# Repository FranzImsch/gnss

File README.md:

# [GNSS Rev. B](https://github.com/FranzImsch/gnss)

# Overview

[ZED-F9P](https://www.u-blox.com/sites/default/files/ZED-F9P-04B_DataSheet_UBX-21044850.pdf)\-based GNSS dev board with [ISM330DHCX](https://www.st.com/resource/en/datasheet/ism330dhcx.pdf) 6-DoF IMU, [BMM150](https://www.bosch-sensortec.com/media/boschsensortec/downloads/datasheets/bst-bmm150-ds001.pdf) Magnetometer and [DPS310](https://www.infineon.com/dgdl/Infineon-DPS310-DS-v01_00-EN.pdf?fileId=5546d462576f34750157750826c42242) pressure sensor.

As a basic UI, the OLED (1.5") can be used along with a navigation switch, more advanced usage requires a web interface. The device features a microSD card reader for data logging.

The ESP32 is used as the microcontroller because of its WiFi and Bluetooth capability that enables data to be streamed onto a device (phone, tablet, …) wirelessly.

The component selection is partly influenced by the semiconductor shortage. The software is yet to be worked on and also the documentation should receive some attention.

# Hardware

The device consists of a stackup of three PCBs. A detailed view is provided by the [3D-model](https://a360.co/38VXSXv). The third PCB is not relevant for the function, as it only serves as a mounting piece for the battery.

 The uppermost PCB of the stackup is where the OLED is mounted along with the navigation switch and some status LEDs. The photo shows the backside of this PCB with the IO ports and their isolation. Also found here is the barometric pressure sensor (top), a port expander and the 12V step-up converter for the OLED. One may ignore the little bodge at the top. :)

 The picture shows the main PCB where the ZED module is located (right-hand side). On the left the ESP32 module can be found along with the FTDI chips for both the ESP and the UART1 port of the ZED-F9P. The bottom left is where the USB hub chip is placed. On the bottom-right there is the power section, consisting of a step-down converter, a power path manager, a fuel gauge for the battery and some super low-noise LDOs for the ZED-F9P.

## Battery

The function of the battery circuitry was tested extensively and no issues were found. The device correctly stops power when the cutoff voltage is reaced (3.2 V, depends on the voltage supervisor). During charging, the unit does not exceed ca. 60°C at the hottest point (which is the power path IC).

## Documentation and Resources

[Schematic](https://franz.science/gnss/Schematic.pdf)  
[iBom PCB #1](https://franz.science/gnss/PCB-1/bom/index.html)  
[iBom PCB #2](https://franz.science/gnss/PCB-2/bom/index.html)

[3D model](https://a360.co/38VXSXv)

## Changelog (Rev A to B)

* Added LiPo battery to enable standalone operation
* Replaced BNO055 with ISM330DHCX and BMM150 due to their superior performance
* Removed SHT40 as the first revision revealed that the board heats up too much for temperature or humidity measurement (Can be added via exposed i2c connector)
* Added USB hub to board
* Protected ZED a bit more against electrical damage (isolating and filtering IO, LDO as power supply)
* many minor improvements

# GNSS in General

Useful literature:

* https://doi.org/10.1007/978-3-211-73017-1
* https://content.u-blox.com/sites/default/files/products/documents/GPS-Compendium_Book\_(GPS-X-02007).pdf?hash=undefined

---

# Licence

Copyright Franz Imschweiler 2022.

This source describes Open Hardware and is licensed under the CERN-OHL-S v2 or any later version. You may redistribute and modify this source and make products using it under the terms of the CERN-OHL-S v2 or any later version (https://ohwr.org/cern_ohl_s_v2.txt).

This source is distributed WITHOUT ANY EXPRESS OR IMPLIED WARRANTY, INCLUDING OF MERCHANTABILITY, SATISFACTORY QUALITY AND FITNESS FOR A PARTICULAR PURPOSE. Please see the CERN-OHL-S v2 for applicable conditions.

Source location: https://github.com/FranzImsch/gnss

As per CERN-OHL-S v2 section 4, should You produce hardware based on this source, You must where practicable maintain the Source Location visible on the external case of the GNSS Receiver or other products you make using this source.

---

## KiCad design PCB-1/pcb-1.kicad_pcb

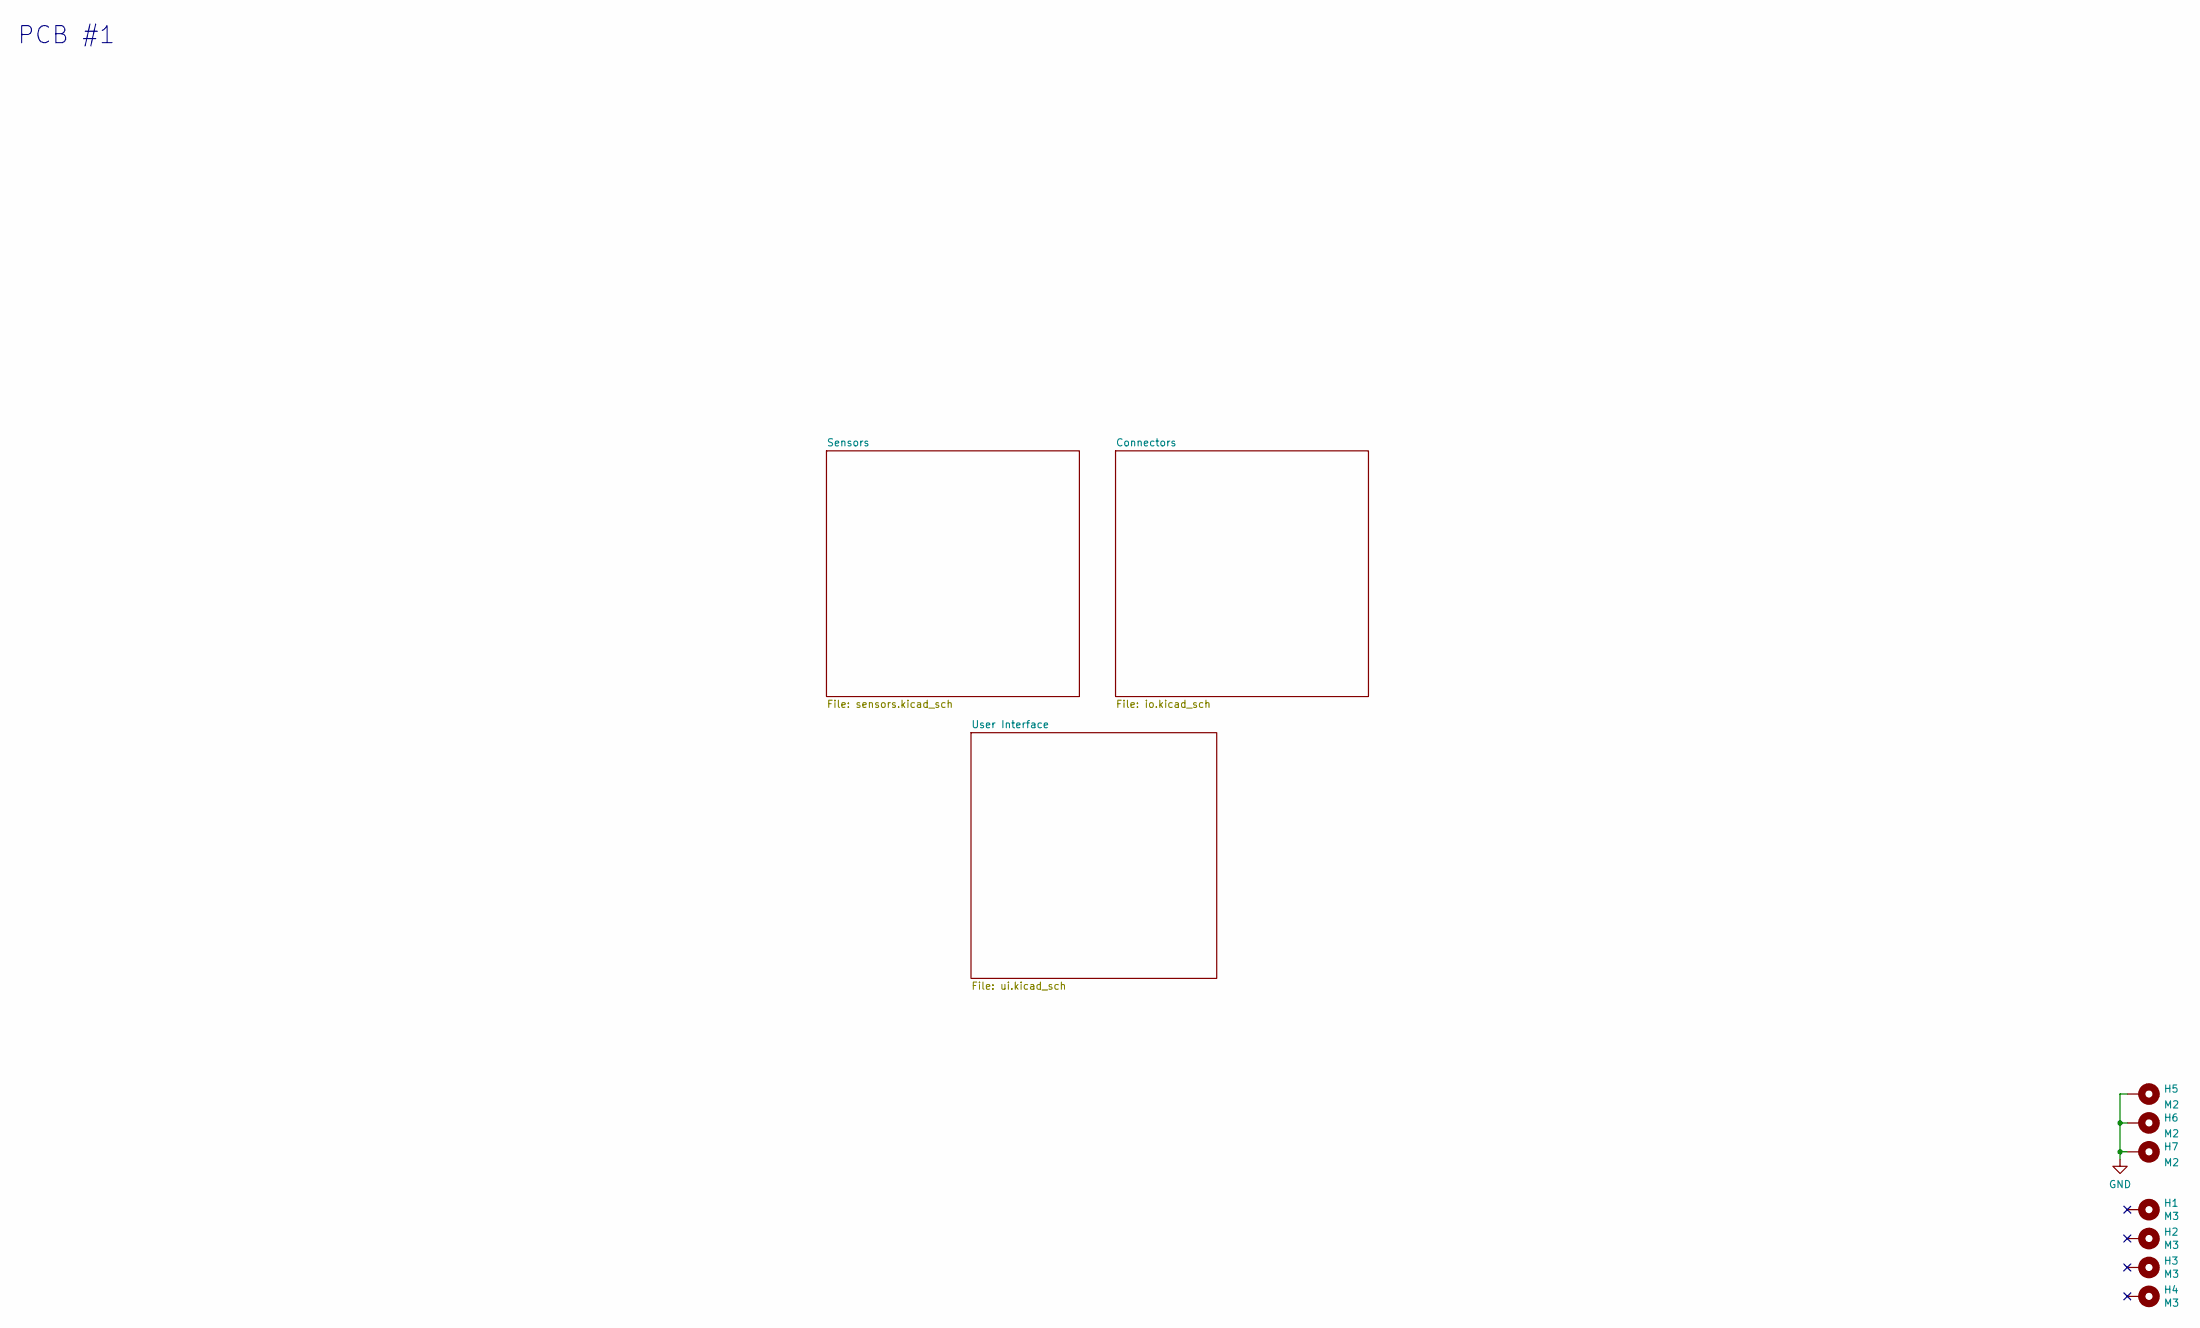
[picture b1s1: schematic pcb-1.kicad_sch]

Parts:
H1, H2, H3, H4: M3; MountingHole_3.2mm_M3_Pad_Via_NoSilk
H5, H6, H7: M2; MountingHole_2.2mm_M2_Pad_Via_NoSilk

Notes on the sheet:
PCB #1

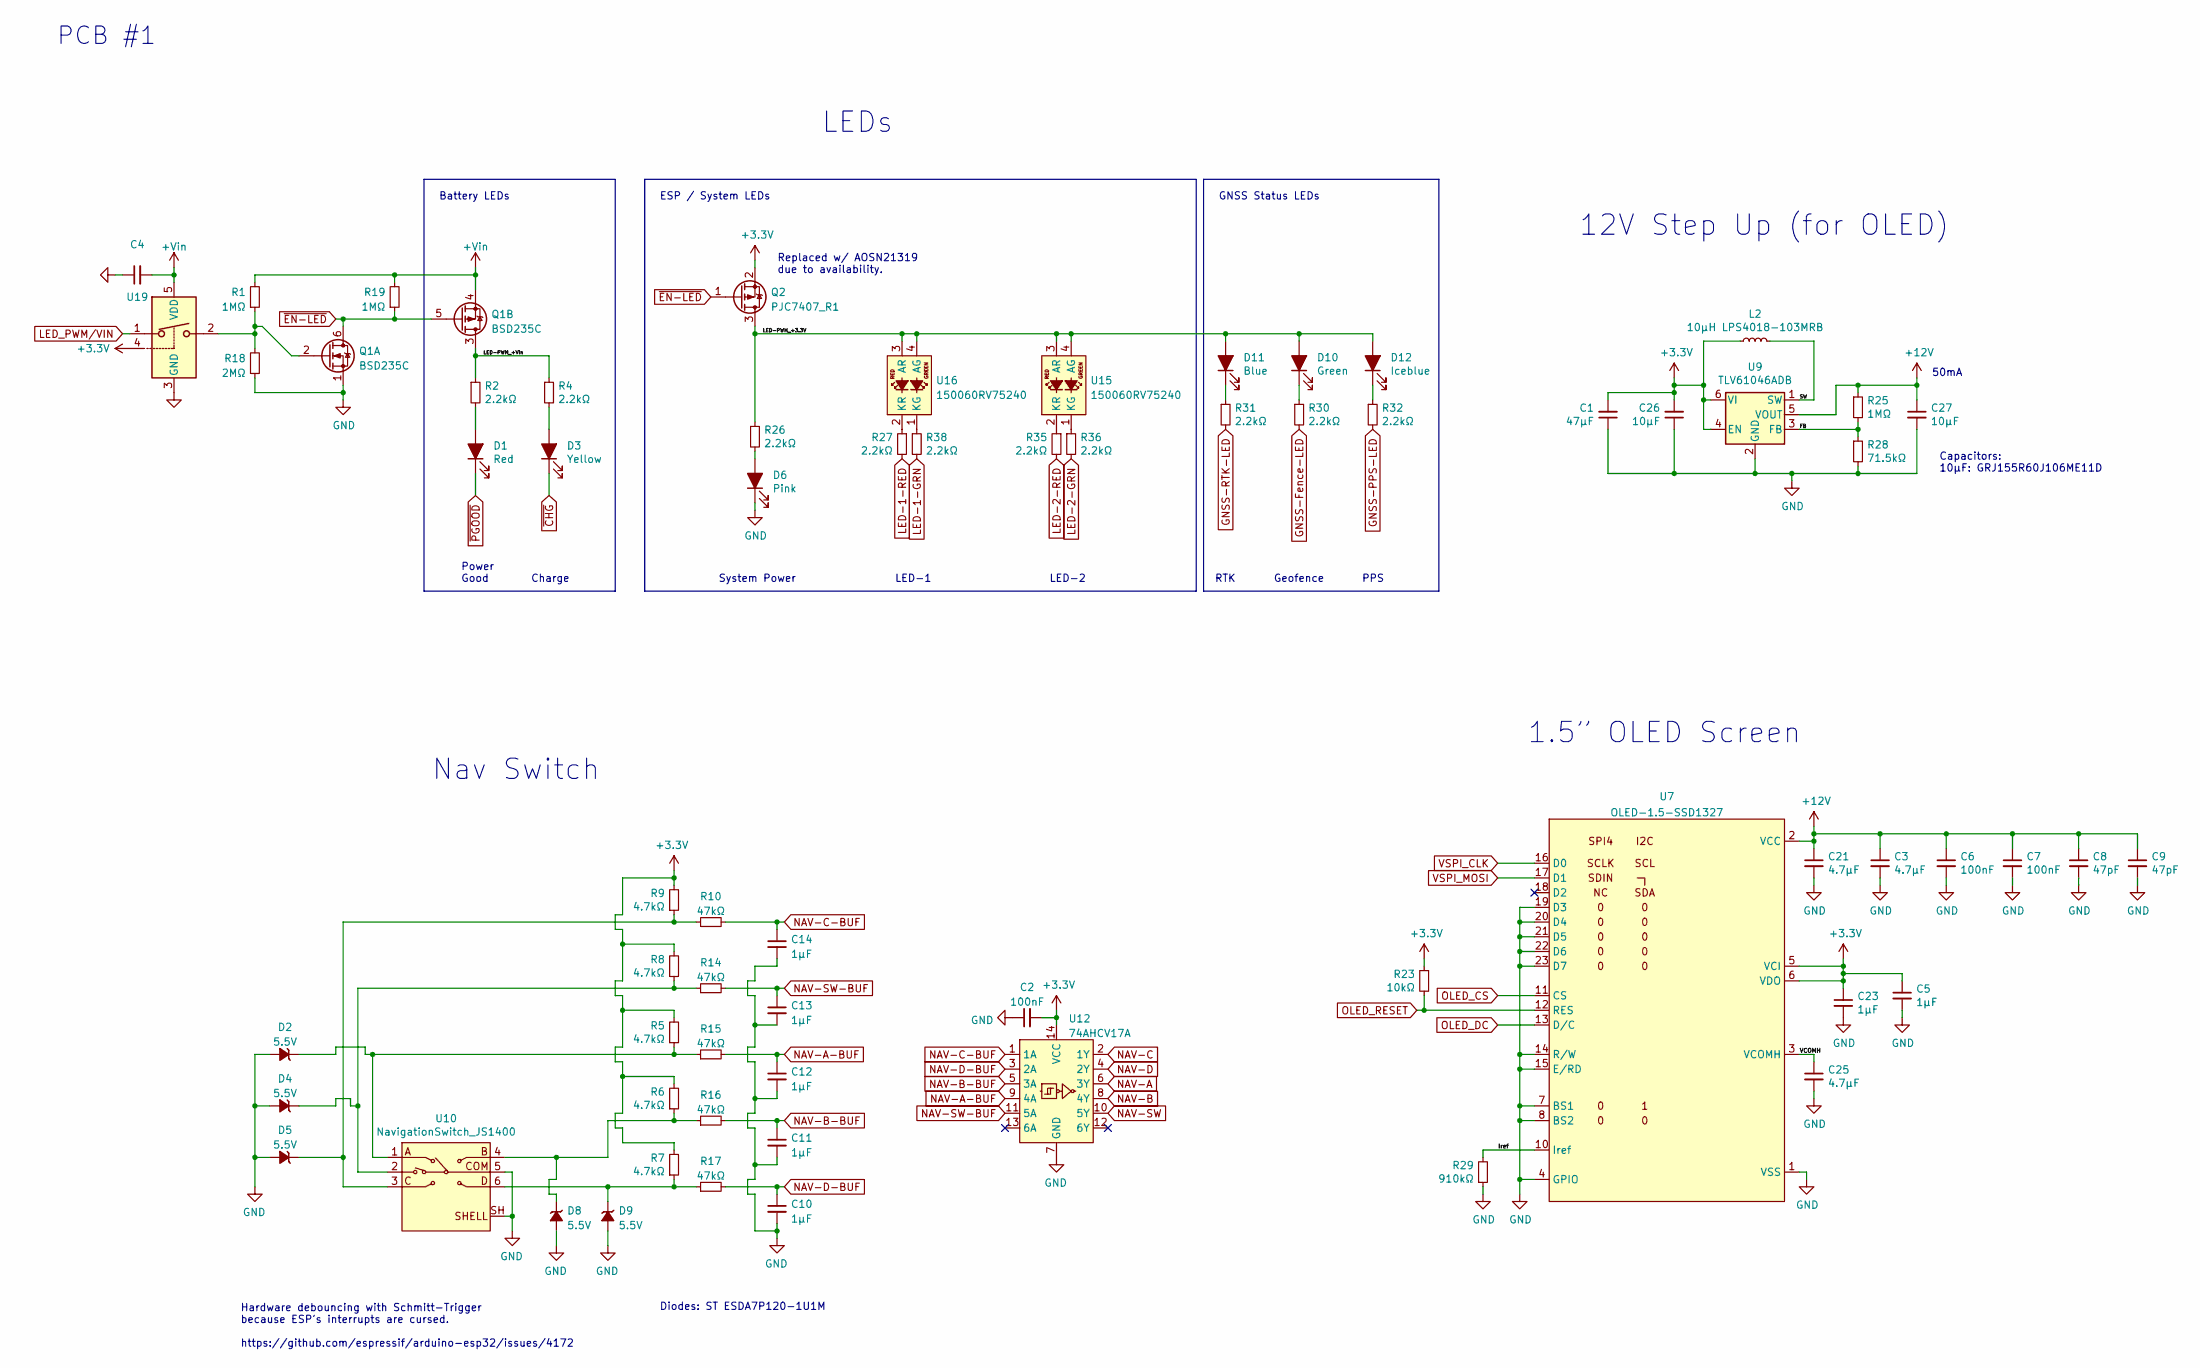
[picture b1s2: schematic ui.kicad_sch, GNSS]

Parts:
C1: 47µF; C_1206_3216Metric_NoSilk
C2: 100nF; C_0402_1005Metric_NoSilk
C3, C21: 4.7µF; C_1206_3216Metric_NoSilk
C4: (no value)
C5, C23: 1µF; C_0603_1608Metric_NoSilk
C6, C7: 100nF; C_0603_1608Metric_NoSilk
C8, C9: 47pF; C_0402_1005Metric_NoSilk
C10, C11, C12, C13, C14: 1µF; C_0402_1005Metric_NoSilk
C25: 4.7µF; C_0603_1608Metric_NoSilk
C26: 10µF; C_0402_1005Metric_NoSilk
C27: 10µF; C_1206_3216Metric_NoSilk
D1: Red; LED_0603_1608Metric_SmallSilk
D2, D4, D5, D8, D9: 5.5V; ST_QFN1610_1_NoSilk
D3: Yellow; LED_0603_1608Metric_SmallSilk
D6: Pink; LED_0603_1608Metric_SmallSilk
D10: Green; LED_0603_1608Metric_SmallSilk
D11: Blue; LED_0603_1608Metric_SmallSilk
D12: Iceblue; LED_0603_1608Metric_SmallSilk
L2: 10µH LPS4018-103MRB; L_Coilcraft_LPS4018_NoSilk
Q1: BSD235C; SOT-363_SC-70-6
Q2: PJC7407_R1; SOT-323_SC-70_NoSilk
R1, R19, R25: 1MΩ; R_0402_1005Metric_NoSilk
R2, R4, R26, R27, R30, R31, R32, R35, R36, R38: 2.2kΩ; R_0402_1005Metric_NoSilk
R5, R6, R7, R8, R9: 4.7kΩ; R_0402_1005Metric_NoSilk
R10, R14, R15, R16, R17: 47kΩ; R_0402_1005Metric_NoSilk
R18: 2MΩ; R_0402_1005Metric_NoSilk
R23: 10kΩ; R_0402_1005Metric_NoSilk
R28: 71.5kΩ; R_0402_1005Metric_NoSilk
R29: 910kΩ; R_0402_1005Metric_NoSilk
U7: OLED-1.5-SSD1327; OLED_SSD1327_1.5
U9: TLV61046ADB; SOT-23-6_NoSilk
U10: NavigationSwitch_JS1400; NavigationStick_ESwitch-JS1400AFQ
U12: 74AHCV17A; TSSOP-14_4.4x5mm_P0.65mm_NoSilk
U15, U16: 150060RV75240; 150060RV75240_Smaller
U19: (no value)

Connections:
+3V3: C1.2, C2.2, C5.1, C23.1, C26.2, L2.1, Q2.2 (S), R5.2, R6.2, R7.2, R8.2, R9.2, R23.1, U7.5 (VCI), U7.6 (VDO), U9.4 (EN), U9.6 (VI), U12.14 (VCC), U19.4; also elsewhere on the board
+12V: C3.1, C6.1, C7.1, C8.1, C9.1, C21.1, C27.1, R25.1, U7.2 (VCC), U7.24 (VCC), U9.5 (VOUT)
+Vin: C4.2, Q1.4 (SP), R1.2, R19.2, U19.5 (VDD); also elsewhere on the board
/User Interface/FB: R25.2, R28.1, U9.3 (FB)
/User Interface/Iref: R29.2, U7.10 (Iref)
/User Interface/LED-PWM_+3.3V: D10.2 (A), D11.2 (A), D12.2 (A), Q2.3 (D), R26.1, U15.3 (AR), U15.4 (AG), U16.3 (AR), U16.4 (AG)
/User Interface/LED-PWM_+Vin: Q1.3 (DP), R2.1, R4.1
/User Interface/SW: L2.2, U9.1 (SW)
/User Interface/VCOMH: C25.1, U7.3 (VCOMH)
GNSS-Fence-LED: R30.2; also elsewhere on the board
GNSS-PPS-LED: R32.2; also elsewhere on the board
GNSS-RTK-LED: R31.2; also elsewhere on the board
LED-1-GRN: R38.2; also elsewhere on the board
LED-1-RED: R27.2; also elsewhere on the board
LED-2-GRN: R36.2; also elsewhere on the board
LED-2-RED: R35.2; also elsewhere on the board
LED_PWM/VIN: U19.1; also elsewhere on the board
NAV-A: U12.6 (3Y); also elsewhere on the board
NAV-A-BUF: C12.1, R15.2, U12.9 (4A)
NAV-B: U12.8 (4Y); also elsewhere on the board
NAV-B-BUF: C11.1, R16.2, U12.5 (3A)
NAV-C: U12.2 (1Y); also elsewhere on the board
NAV-C-BUF: C14.1, R10.2, U12.1 (1A)
NAV-D: U12.4 (2Y); also elsewhere on the board
NAV-D-BUF: C10.1, R17.2, U12.3 (2A)
NAV-SW: U12.10 (5Y); also elsewhere on the board
NAV-SW-BUF: C13.1, R14.2, U12.11 (5A)
unnamed: D1.2 (A), R2.2
unnamed: D2.1 (K), R5.1, R15.1, U10.1 (A)
unnamed: D3.2 (A), R4.2
unnamed: D4.1 (K), R8.1, R14.1, U10.2 (BTN)
unnamed: D5.1 (K), R9.1, R10.1, U10.3 (C)
unnamed: D6.2 (A), R26.2
unnamed: D8.1 (K), R6.1, R16.1, U10.4 (B)
unnamed: D9.1 (K), R7.1, R17.1, U10.6 (D)
unnamed: D10.1 (K), R30.1
unnamed: D11.1 (K), R31.1
unnamed: D12.1 (K), R32.1
unnamed: Q1.2 (GN), R1.1, R18.2, U19.2
unnamed: R27.1, U16.2 (KR)
unnamed: R35.1, U15.2 (KR)
unnamed: R36.1, U15.1 (KG)
unnamed: R38.1, U16.1 (KG)
OLED_CS: U7.11 (CS); also elsewhere on the board
OLED_DC: U7.13 (D/C); also elsewhere on the board
OLED_RESET: R23.2, U7.12 (RES); also elsewhere on the board
VSPI_CLK: U7.16 (D0); also elsewhere on the board
VSPI_MOSI: U7.17 (D1); also elsewhere on the board
~CHG: D3.1 (K); also elsewhere on the board
~EN-LED: Q1.5 (GP), Q1.6 (DN), Q2.1 (G), R19.1
~PGOOD: D1.1 (K); also elsewhere on the board

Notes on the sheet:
Hardware debouncing with Schmitt-Trigger because ESP's interrupts are cursed. https://github.com/espressif/arduino-esp32/issues/4172
Nav Switch
PCB #1
ESP / System LEDs
PPS
1.5” OLED Screen
RTK
System Power
Diodes: ST ESDA7P120-1U1M
50mA
Replaced w/ AOSN21319 due to availability.
12V Step Up (for OLED)
Battery LEDs
Power Good
Charge
GNSS Status LEDs
Capacitors: 10µF: GRJ155R60J106ME11D
LEDs
Geofence
LED-1
LED-2

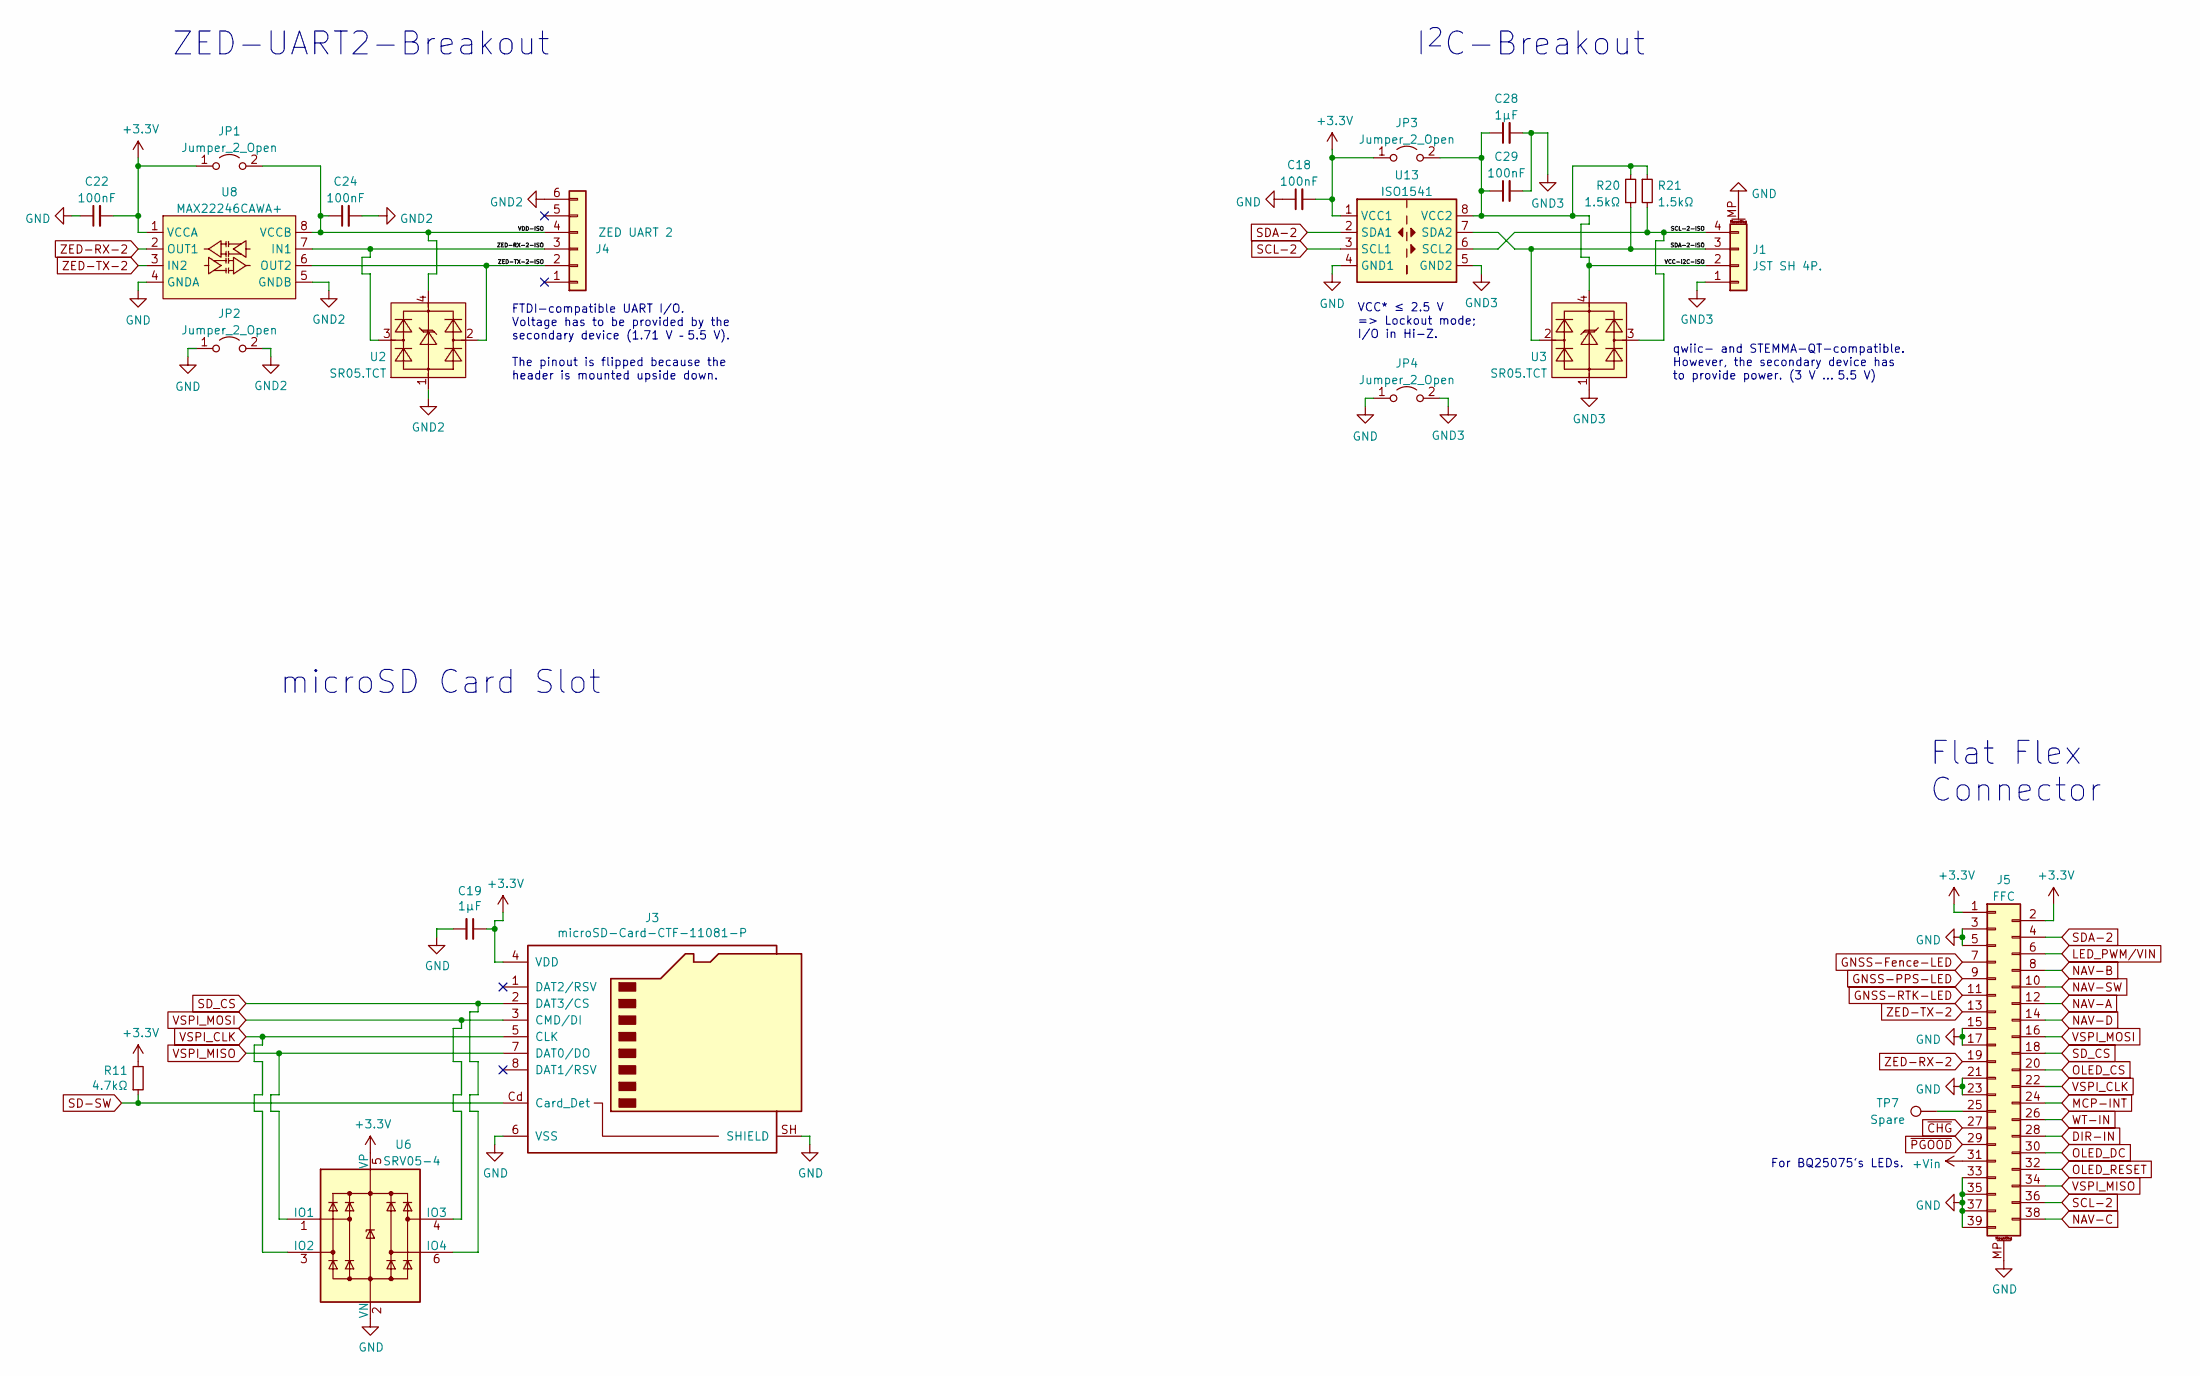
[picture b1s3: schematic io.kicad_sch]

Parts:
C18, C22, C24, C29: 100nF; C_0402_1005Metric_NoSilk
C19, C28: 1µF; C_0402_1005Metric_NoSilk
J1: JST SH 4P.; JST_SH_SM04B-SRSS-TB_1x04-1MP_P1.00mm_Horizontal
J3: microSD-Card-CTF-11081-P
J4: ZED UART 2; PinSocket_2.54mm_01x06_Horizontal_SMD
J5: FFC; 5025983993
JP1, JP2, JP3, JP4: Jumper_2_Open; R_0805_2012Metric_NoSilk_DNP
R11: 4.7kΩ; R_0402_1005Metric_NoSilk
R20, R21: 1.5kΩ; R_0402_1005Metric_NoSilk
TP7: Spare; TestPoint_Pad_D1.0mm_NoSIlk
U2, U3: SR05.TCT; SOT143-4L-slim
U6: SRV05-4; SOT-23-6_NoSilk
U8: MAX22246CAWA+; SOIC-8W_3.9x_P1.27mm_NoSilk
U13: ISO1541; SOIC-8_3.9x4.9mm_P1.27mm_NoSilk

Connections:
+3V3: C18.2, C19.1, C22.2, J3.4 (VDD), J5.1, J5.2, JP1.1 (A), JP3.1 (A), R11.2, U6.5 (VP), U8.1 (VCCA), U13.1 (VCC1); also elsewhere on the board
+Vin: J5.31; also elsewhere on the board
/Connectors/SCL-2-ISO: J1.4, R21.2, U3.3 (CH2), U13.6 (SCL2)
/Connectors/SDA-2-ISO: J1.3, R20.1, U3.2 (CH1), U13.7 (SDA2)
/Connectors/VCC-I2C-ISO: C28.1, C29.1, J1.2, JP3.2 (B), R20.2, R21.1, U3.4 (VBUS), U13.8 (VCC2)
/Connectors/VDD-ISO: C24.1, J4.4, JP1.2 (B), U2.4 (VBUS), U8.8 (VCCB)
/Connectors/ZED-RX-2-ISO: J4.3, U2.3 (CH2), U8.7 (IN1)
/Connectors/ZED-TX-2-ISO: J4.2, U2.2 (CH1), U8.6 (OUT2)
DIR-IN: J5.28; also elsewhere on the board
GND2: C24.2, J4.6, JP2.2 (B), U2.1 (GND), U8.5 (GNDB)
GND3: C28.2, C29.2, J1.1, JP4.2 (B), U3.1 (GND), U13.5 (GND2)
GNSS-Fence-LED: J5.7; also elsewhere on the board
GNSS-PPS-LED: J5.9; also elsewhere on the board
GNSS-RTK-LED: J5.11; also elsewhere on the board
LED_PWM/VIN: J5.6; also elsewhere on the board
MCP-INT: J5.24; also elsewhere on the board
NAV-A: J5.12; also elsewhere on the board
NAV-B: J5.8; also elsewhere on the board
NAV-C: J5.38; also elsewhere on the board
NAV-D: J5.14; also elsewhere on the board
NAV-SW: J5.10; also elsewhere on the board
unnamed: J5.25, TP7.1
OLED_CS: J5.20; also elsewhere on the board
OLED_DC: J5.30; also elsewhere on the board
OLED_RESET: J5.32; also elsewhere on the board
SCL-2: J5.36, U13.3 (SCL1); also elsewhere on the board
SD-SW: J3.Cd (Card_Det), R11.1; also elsewhere on the board
SDA-2: J5.4, U13.2 (SDA1); also elsewhere on the board
SD_CS: J3.2 (DAT3/CS), J5.18, U6.6 (IO4)
VSPI_CLK: J3.5 (CLK), J5.22, U6.3 (IO2); also elsewhere on the board
VSPI_MISO: J3.7 (DAT0/DO), J5.34, U6.1 (IO1)
VSPI_MOSI: J3.3 (CMD/DI), J5.16, U6.4 (IO3); also elsewhere on the board
WT-IN: J5.26; also elsewhere on the board
ZED-RX-2: J5.19, U8.2 (OUT1)
ZED-TX-2: J5.13, U8.3 (IN2)
~CHG: J5.27; also elsewhere on the board
~PGOOD: J5.29; also elsewhere on the board

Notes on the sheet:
I^{2}C-Breakout
VCC* ≤ 2.5 V => Lockout mode; I/O in Hi-Z.
qwiic- and STEMMA-QT-compatible. However, the secondary device has to provide power. (3 V … 5.5 V)
Flat Flex Connector
For BQ25075's LEDs.
microSD Card Slot
FTDI-compatible UART I/O. Voltage has to be provided by the secondary device (1.71 V – 5.5 V). The pinout is flipped because the header is mounted upside down.
ZED-UART2-Breakout

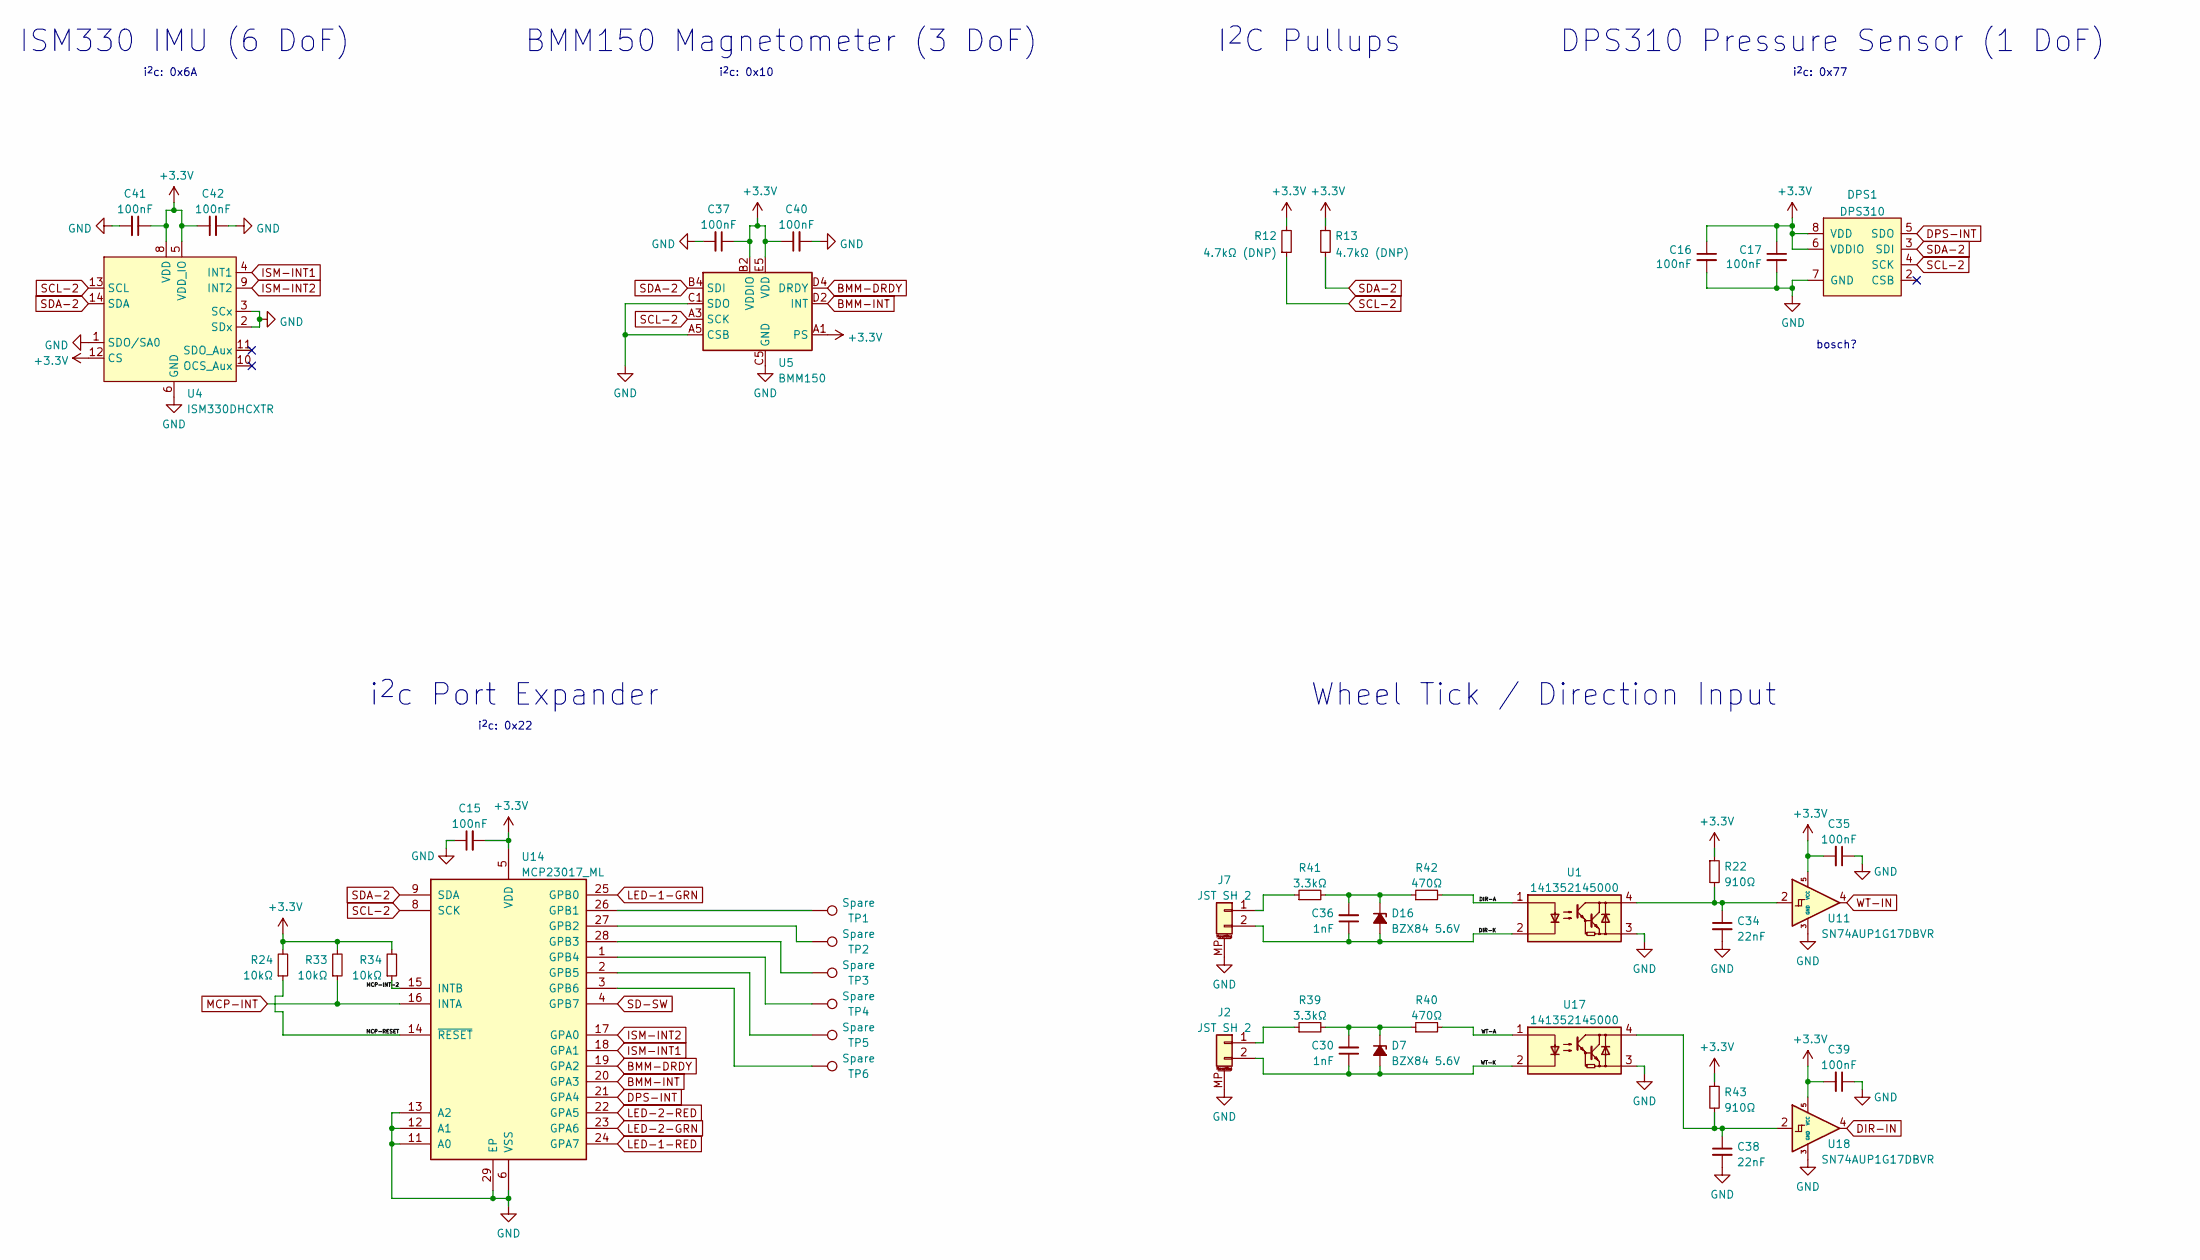
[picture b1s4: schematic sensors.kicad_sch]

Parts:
C15, C16, C17, C35, C37, C39, C40, C41, C42: 100nF; C_0402_1005Metric_NoSilk
C30, C36: 1nF; C_0402_1005Metric_NoSilk
C34, C38: 22nF; C_0402_1005Metric_NoSilk
D7, D16: BZX84 5.6V; SOT-23_NoSilk
DPS1: DPS310
J2, J7: JST SH 2; JST_SH_SM02B-SRSS-TB_1x02-1MP_P1.00mm_Horizontal_NoSilk
R12, R13: 4.7kΩ (DNP); R_0402_1005Metric_NoSilk
R22, R43: 910Ω; R_0402_1005Metric_NoSilk
R24, R33, R34: 10kΩ; R_0402_1005Metric_NoSilk
R39, R41: 3.3kΩ; R_0603_1608Metric_NoSilk
R40, R42: 470Ω; R_0402_1005Metric_NoSilk
TP1, TP2, TP3, TP4, TP5, TP6: Spare; TestPoint_Pad_D1.0mm_NoSIlk
U1, U17: 141352145000
U4: ISM330DHCXTR; LGA-14L_1.5x3.0x0.86_ST
U5: BMM150; WLCSP-12_1.56x1.56mm_P0.4mm_NoSilk
U11, U18: SN74AUP1G17DBVR; SOT-23-5_NoSilk
U14: MCP23017_ML; QFN-28-1EP_6x6mm_P0.65mm_EP4.25x4.25mm_NoSilk

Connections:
+3V3: C15.2, C16.1, C17.1, C35.2, C37.1, C39.2, C40.1, C41.1, C42.1, DPS1.6 (VDDIO), DPS1.8 (VDD), R12.2, R13.1, R22.1, R24.2, R33.2, R34.2, R43.1, U4.5 (VDD_IO), U4.8 (VDD), U4.12 (CS), U5.A1 (PS), U5.B2 (VDDIO), U5.E5 (VDD), U11.5 (VCC), U14.5 (VDD), U18.5 (VCC); also elsewhere on the board
/Sensors/DIR-A: R42.2, U1.1
/Sensors/DIR-K: C36.1, D16.1 (A), J7.2, U1.2
/Sensors/MCP-INT-2: R34.1, U14.15 (INTB)
/Sensors/MCP-RESET: R24.1, U14.14 (~RESET)
/Sensors/WT-A: R40.2, U17.1
/Sensors/WT-K: C30.1, D7.1 (A), J2.2, U17.2
BMM-DRDY: U5.D4 (DRDY), U14.19 (GPA2)
BMM-INT: U5.D2 (INT), U14.20 (GPA3)
DIR-IN: U18.4; also elsewhere on the board
DPS-INT: DPS1.5 (SDO), U14.21 (GPA4)
ISM-INT1: U4.4 (INT1), U14.18 (GPA1)
ISM-INT2: U4.9 (INT2), U14.17 (GPA0)
LED-1-GRN: U14.25 (GPB0); also elsewhere on the board
LED-1-RED: U14.24 (GPA7); also elsewhere on the board
LED-2-GRN: U14.23 (GPA6); also elsewhere on the board
LED-2-RED: U14.22 (GPA5); also elsewhere on the board
MCP-INT: R33.1, U14.16 (INTA); also elsewhere on the board
unnamed: C30.2, D7.3 (K), R39.2, R40.1
unnamed: C34.1, R22.2, U1.4, U11.2
unnamed: C36.2, D16.3 (K), R41.2, R42.1
unnamed: C38.1, R43.2, U17.4, U18.2
unnamed: J2.1, R39.1
unnamed: J7.1, R41.1
unnamed: TP1.1, U14.26 (GPB1)
unnamed: TP2.1, U14.27 (GPB2)
unnamed: TP3.1, U14.28 (GPB3)
unnamed: TP4.1, U14.1 (GPB4)
unnamed: TP5.1, U14.2 (GPB5)
unnamed: TP6.1, U14.3 (GPB6)
SCL-2: DPS1.4 (SCK), R12.1, U4.13 (SCL), U5.A3 (SCK), U14.8 (SCK); also elsewhere on the board
SD-SW: U14.4 (GPB7); also elsewhere on the board
SDA-2: DPS1.3 (SDI), R13.2, U4.14 (SDA), U5.B4 (SDI), U14.9 (SDA); also elsewhere on the board
WT-IN: U11.4; also elsewhere on the board

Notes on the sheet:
ISM330 IMU (6 DoF)
i^{2}c: 0x10
i^{2}c: 0x77
i^{2}c: 0x6A
i^{2}c Port Expander
DPS310 Pressure Sensor (1 DoF)
I^{2}C Pullups
i^{2}c: 0x22
Wheel Tick / Direction Input
BMM150 Magnetometer (3 DoF)
bosch?

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
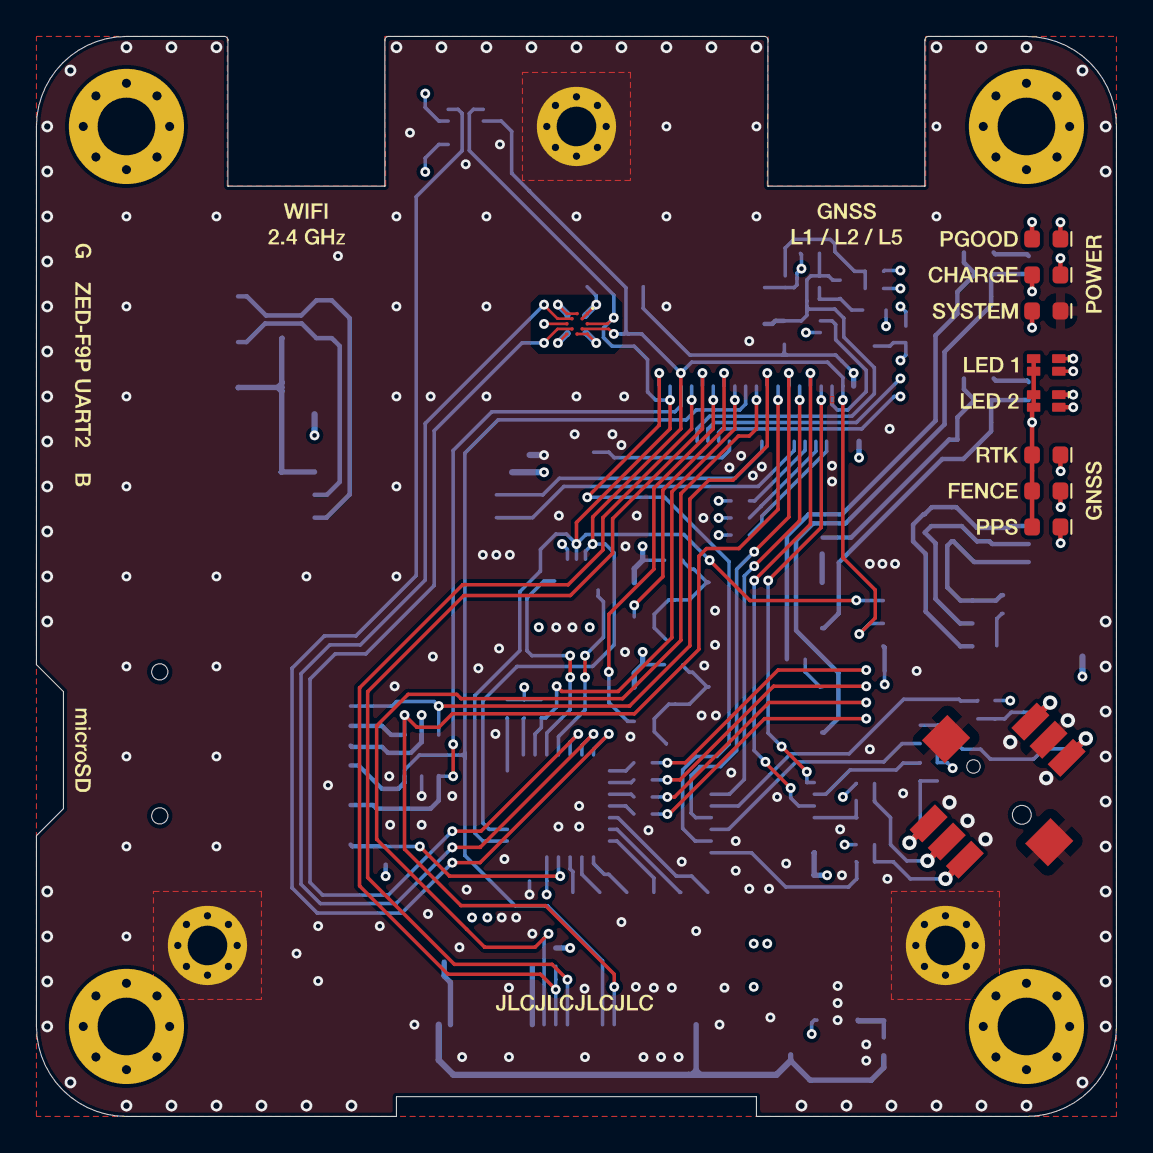
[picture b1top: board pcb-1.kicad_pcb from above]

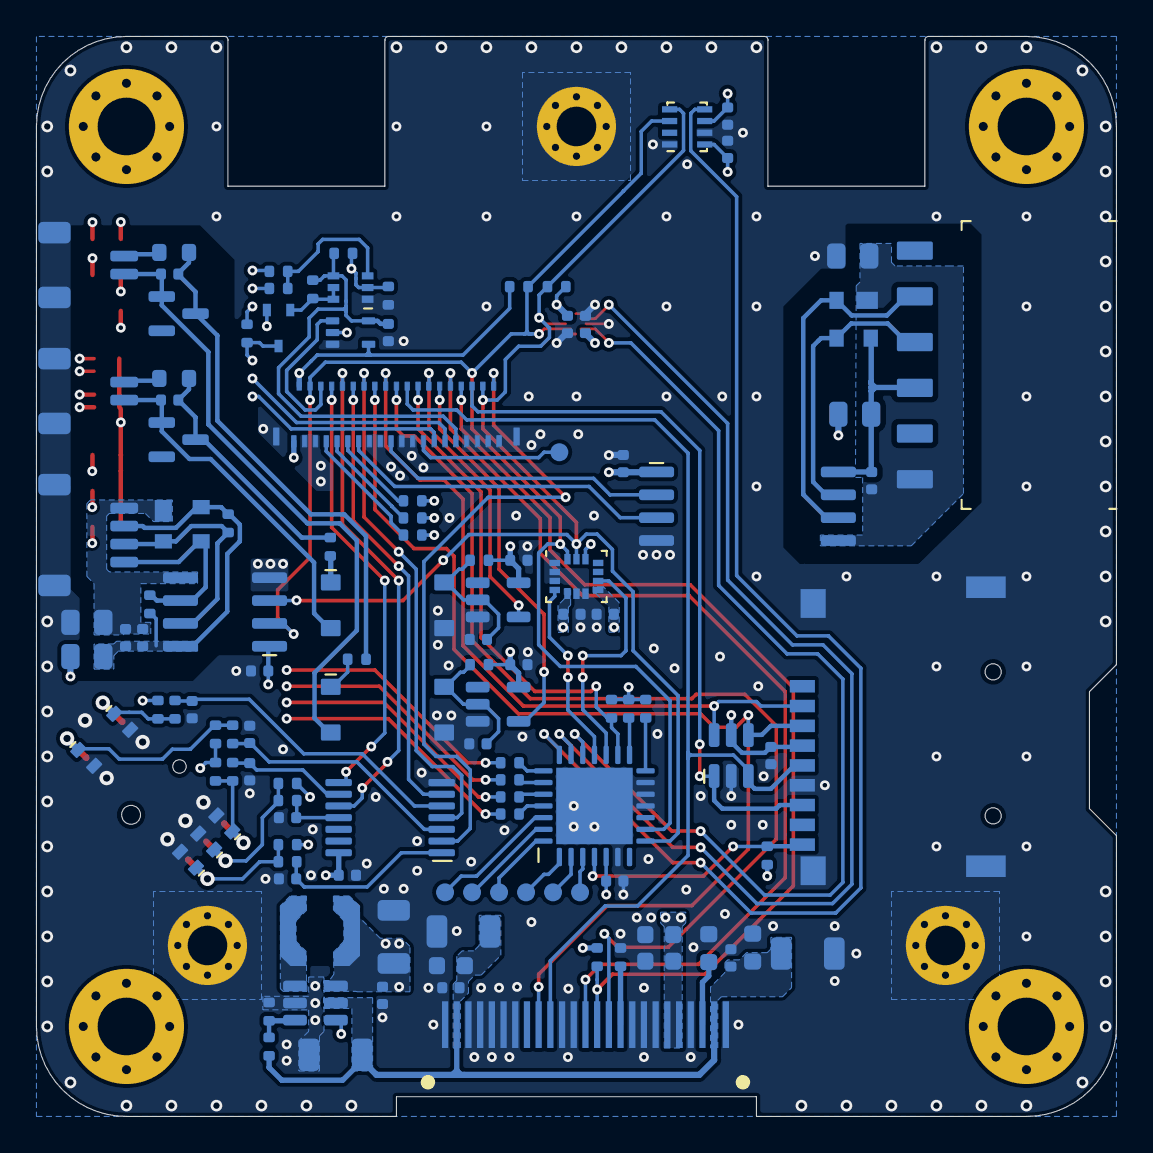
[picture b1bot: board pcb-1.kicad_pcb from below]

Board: 4 copper layers, 60.0 x 60.0 mm, 139 parts (121 on the bottom side), 94 nets.

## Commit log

2022-05-26 finalised Hardware Rev. B
2022-10-11 added photos to docu
